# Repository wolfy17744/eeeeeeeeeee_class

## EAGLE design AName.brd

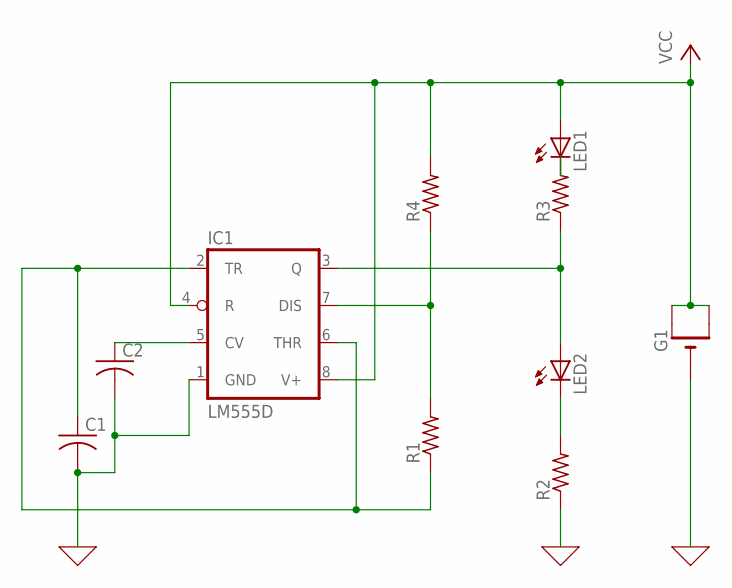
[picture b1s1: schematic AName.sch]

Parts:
C1, C2: C-USC0805; C0805
G1: CR1220THM; CR1220-THM
IC1: LM555D; SO08
LED1, LED2: LED5MM
R1, R2, R4: R-US_R0805; R0805
R3: R-US_M0805; M0805

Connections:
0: C1.2, C2.2, G1.-, IC1.1 (GND), R2.1
unnamed: C1.1, IC1.2 (TR), IC1.6 (THR), R1.1
unnamed: C2.1, IC1.5 (CV)
unnamed: LED2.K (C), R2.2
unnamed: IC1.3 (Q), LED2.A, R3.1
unnamed: LED1.K (C), R3.2
unnamed: IC1.7 (DIS), R1.2, R4.1
VCC: G1.+1 (+), G1.+2 (+1), IC1.4 (R), IC1.8 (V+), LED1.A, R4.2

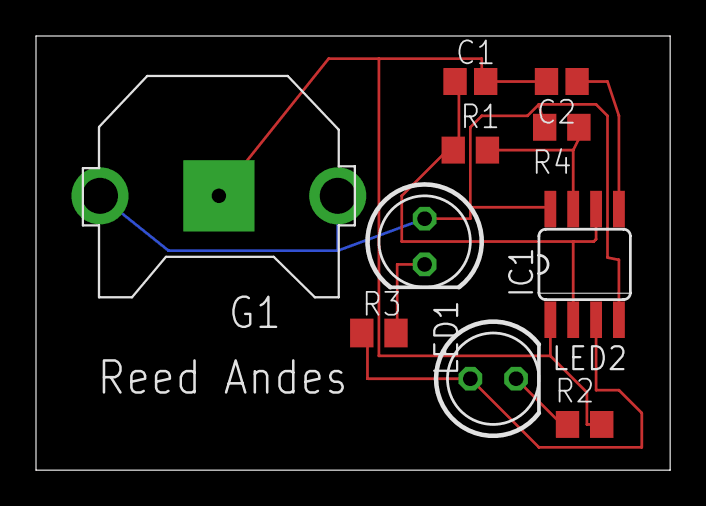
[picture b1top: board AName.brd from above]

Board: 2 copper layers, 35.2 x 24.1 mm, 10 parts (0 on the bottom side), 8 nets.

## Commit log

2018-05-08 TH was wired to VDD. Fixed ERC errors.
